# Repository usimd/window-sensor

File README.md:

# BLE window sensor for Homeassistant

BLE window/door sensor built around the u-blox NORA-B226 (nRF54L10). Broadcasts open/closed/tilt state via BTHome v2 non-connectable advertising. MCUboot OTA-capable.

## Hardware

- **MCU**: nRF54L10 (Cortex-M33, 1 MiB RRAM, 192 KB RAM) in u-blox NORA-B226-00B module
- **Sensor**: TMAG5273 3D Hall-effect sensor for contactless magnet detection
- **Power**: CR14250 (½AA) lithium cell, target multi-year battery life
- **Enclosure**: 3D-printed case with magnet holder (FreeCAD, `case/`)

## Firmware

Rust + Embassy async runtime, BLE via nrf-sdc + trouble-host.

- Non-connectable BTHome v2 advertising (open / closed / tilt)
- MCUboot bootloader with ed25519-signed OTA images
- Host-side unit tests for classifier and gesture logic

## Repository Structure

| Path | Description |
|---|---|
| `*.kicad_*` | KiCad 10 schematic, PCB, and project files |
| `lib/` | Local symbol/footprint libraries and 3D models |
| `firmware/` | Rust firmware (Embassy, BLE, MCUboot support) |
| `firmware/mcuboot/` | MCUboot config and partition overlay |
| `case/` | FreeCAD enclosure design and 3MF exports |
| `scripts/` | BLE scanner and dev utilities |
| `sim/` | Magnetic simulation data |

## Building

```bash
# Install toolchain
rustup target add thumbv8m.main-none-eabihf
cargo install just cargo-binutils

# Build, lint, test
just ci

# Flash (requires probe-rs + debug probe)
just run
```

## License

Dual-licensed: hardware under CERN-OHL-W-2.0, firmware under Apache-2.0. See [`LICENSE`](LICENSE).

## AISLER discount

In case you want to build this (or any other) project at AISLER, here's a 10€ discount code for you: `MakeInEurope-ZDCTN`.

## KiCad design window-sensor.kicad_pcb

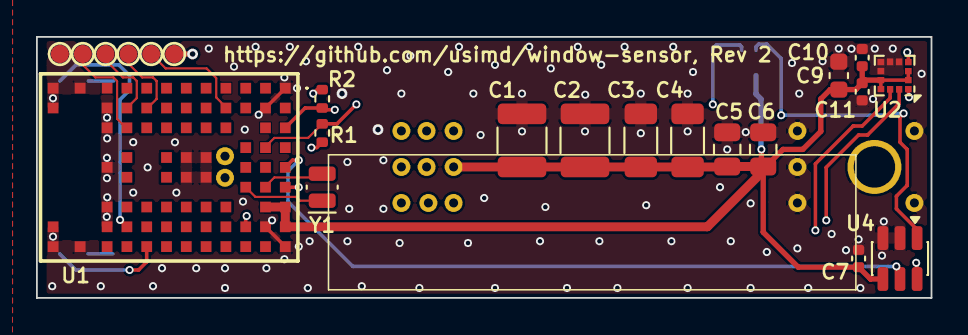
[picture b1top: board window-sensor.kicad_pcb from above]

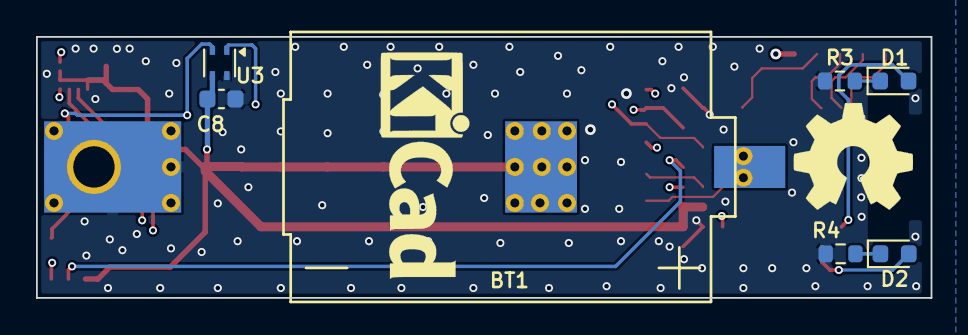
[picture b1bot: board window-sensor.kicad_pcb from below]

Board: 4 copper layers, 49.7 x 14.5 mm, 24 parts (7 on the bottom side), 17 nets.

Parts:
BT1: 1/2 AA LiSOCl2 3.6V 1200mAh; Battery_0.5AA_Keystone_557_5331
C1, C2: 47uF 10V X7R; C_1210_3225Metric
C3, C4: 22uF 10V X7R; C_1206_3216Metric
C5, C6: 10uF 10V X7R; C_0805_2012Metric
C7, C10, C11: 1uF; C_0402_1005Metric
C8: 1uF; C_0603_1608Metric
C9: 10uF; C_0603_1608Metric
D1: Blue; LED_0603_1608Metric
D2: Red; LED_0603_1608Metric
J1: Conn_01x06; Conn_01x06_PogoPins_1.27mm
R1, R2: 16.9k; R_0402_1005Metric
R3: 60.4; R_0603_1608Metric
R4: 160; R_0603_1608Metric
U1: NORA-B216-00B; NORAB22600B
U2: LIS2DTW12TR; LGA-12_2x2mm_P0.5mm
U3: SHT4x; Sensirion_DFN-4_1.5x1.5mm_P0.8mm_SHT4x_NoCentralPad
U4: TMAG5273; SOT-23-6
Y1: 32.768kHz; Crystal_SMD_MicroCrystal_CC8V-T1A-2Pin_2.0x1.2mm

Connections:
+BATT: BT1.1 (+), C1.1, C2.1, C3.1, C4.1, C5.1, C6.1, C7.1, C8.1, C9.1, C10.1, C11.1, J1.1, R1.1, R2.1, U1.A7 (VCC), U1.A8 (VCC_2), U1.B7 (VCC_3), U2.2 (~CS), U2.3 (SA0/SDO), U2.9 (Vdd), U2.10 (Vdd_IO), U3.3 (VDD), U4.4 (VCC)
/HALL: U1.A5 (GPIO_1), U4.5 (~INT)
/MEMS_INT1: U1.A6 (GPIO_2), U2.12 (INT1)
/MEMS_INT2: U1.C8 (GPIO_3), U2.11 (INT2)
/SCL: R2.2, U1.A3 (I2C_SCL), U2.1 (SCL/SPC), U3.2 (SCL), U4.1 (SCL)
/SDA: R1.2, U1.B4 (I2C_SDA), U2.4 (SDA/SDI), U3.1 (SDA), U4.6 (SDA)
/SWCLK: J1.4, U1.J2 (SWDCLK)
/SWDIO: J1.3, U1.H2 (SWDIO)
/UART_TX: J1.2, U1.D2 (QSPI_D0)
/~RESET: J1.5, U1.J3 (RESET_N)
GND: BT1.2 (-), C1.2, C2.2, C3.2, C4.2, C5.2, C6.2, C7.2, C8.2, C9.2, C10.2, C11.2, J1.6, R3.2, R4.2, U1.A1 (GND), U1.A9 (VSS_2), U1.B2 (VSS_3), U1.B8 (VSS_4), U1.E4 (VSS_5), U1.E5 (VSS_6), U1.F4 (VSS_7), U1.F5 (VSS_8), U1.K2 (VSS_9), U1.K3 (VSS_10), U1.K5 (VSS_11), U1.K7 (VSS_12), U1.K8 (VSS_13), U1.L1 (EAGP_1), U1.L9 (EAGP_2), U1.M1 (EAGP_3), U1.M2 (EAGP_4), U1.M8 (EAGP_5), U1.M9 (EAGP_6), U2.5 (RES), U2.6 (GND), U2.7 (GND), U2.8 (GND), U3.4 (VSS), U4.2 (GND), U4.3 (TEST)
unnamed: D1.2 (A), U1.J8 (GPIO_8)
unnamed: D1.1 (K), R3.1
unnamed: D2.2 (A), U1.H9 (GPIO_7)
unnamed: D2.1 (K), R4.1
unnamed: U1.B6 (XTAL_32K_1), Y1.2
unnamed: U1.C6 (XTAL_32K_2), Y1.1

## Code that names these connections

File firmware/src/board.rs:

//! Pin assignments for NORA-B216 module (nRF54L10)
//!
//! Derived from PCB netlist (window-sensor.kicad_pcb) — this is the source of truth.
//!
//! NORA-B216 module pin → nRF54L10 GPIO mapping (from UBX-24071142 product spec):
//!   A3 (I2C_SCL)  → P1.02
//!   B4 (I2C_SDA)  → P1.03
//!   A5 (GPIO_1)   → P1.04  → /HALL (TMAG5273 INT)
//!   A6 (GPIO_2)   → P1.05  → /MEMS_INT1 (LIS2DTW12 INT1)
//!   C8 (GPIO_3)   → P1.06  → /MEMS_INT2 (LIS2DTW12 INT2)
//!   H9 (GPIO_7)   → P1.10  → LED D2 (Red) anode
//!   J8 (GPIO_8)   → P1.08  → LED D1 (Blue) anode
//!   D2 (UART_TX)  → P1.01  → UART TX (debug telemetry)
//!
//! LEDs are active-high: GPIO drives anode, cathode through resistor to GND.

use embassy_nrf::peripherals;

// I2C bus (shared: TMAG5273 @ 0x22, LIS2DTW12 @ 0x19, SHT4x @ 0x44)
pub type I2cScl = peripherals::P1_02;
pub type I2cSda = peripherals::P1_03;

// Hall sensor interrupt (active-low, wake-from-sleep trigger)
pub type HallInt = peripherals::P1_04;

// MEMS accelerometer interrupts
pub type MemsInt1 = peripherals::P1_05;
pub type MemsInt2 = peripherals::P1_06;

// LEDs (active-high drive)
pub type LedBlue = peripherals::P1_08;
pub type LedRed = peripherals::P1_10;

// Debug UART TX
pub type UartTx = peripherals::P1_01;

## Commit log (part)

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2026-06-01 Initial commit: PCB, firmware, CI pipelines
    - KiCad 9 schematic + PCB (nRF54L10 / NORA-B226-00B)
    - Custom footprints + STEP models with attribution
    - Embassy/Rust firmware (BTHome v2, MCUboot OTA)
    - CI: build/test/lint + release workflow with image signing
    - Dual license: CERN-OHL-W-2.0 (hardware) + Apache-2.0 (firmware)
2026-06-01 fix(ci): use kicad/kicad:10.0 container + fix cargo fmt
    - Schematic is KiCad 10 format, sparkengineering/kicad-action@v4 ships KiCad 9
    - Replace action with direct kicad-cli commands in kicad/kicad:10.0 container
    - Fix formatting in mems.rs (long assert_eq line)
2026-06-01 fix(ci): docker run for kicad, --no-sysbuild for mcuboot
    - KiCad: container: directive breaks actions/checkout permissions;
    use docker run with volume mount instead
    - MCUboot: nRF Connect SDK v2.9.0 defaults to sysbuild which wraps
    MCUboot in multi-image build; --no-sysbuild builds bootloader standalone
2026-06-01 refactor(ci): use just recipes, bump NCS to v3.3.0, fix permissions
    - CI firmware job now calls 'just ci' + 'just sign' — same as local dev
    - KiCad docker: add --user to fix permission denied on report files
    - MCUboot: bump nRF Connect SDK to v3.3.0 (nRF54L10 board support)
    - Fix objcopy: use rust-objcopy directly (cargo objcopy arg parsing)
    - justfile: ci recipe now includes soc-heater variants, size uses cargo-binutils
2026-06-01 fix(ci): board is nrf54l15dk/nrf54l10/cpuapp in NCS v3.3.0
    The nRF54L10 doesn't have its own DK board definition in Zephyr 4.3;
    it's targeted as a SoC variant on the nRF54L15 DK.
2026-06-01 fix(ci): just var syntax, KiCad HOME=/tmp for symbol resolution
    - just variable overrides go BEFORE recipe name, not after
    - KiCad container needs HOME=/tmp so it can write .config/kicad/
    and resolve project sym-lib-table (fixes 66 phantom ERC violations)
2026-06-01 fix(ci): absolute paths for objcopy, root user for KiCad, Zephyr SDK
    - justfile objcopy: use justfile_directory() for absolute paths (fixes
    'No such file' on CI where cwd may differ)
    - KiCad docker: use --user 0:0 (root can write reports AND access
    /usr/share/kicad/template/sym-lib-table for standard symbols)
    - Release: install Zephyr SDK v0.17.0 (arm-zephyr-eabi toolchain)
    - Release: fix cargo objcopy → rust-objcopy (same arg-parsing fix)
2026-06-01 fix(ci): track .cargo/config.toml, fix KiCad sym-lib resolution
    - Add firmware/.cargo/config.toml to git (was untracked, causing cargo
    to build for x86_64 host instead of thumbv8m.main-none-eabihf on CI)
    - Copy global sym-lib-table into root's config in Docker containers so
    kicad-cli resolves standard symbol libraries when running as --user 0:0
    - Fix partitions.overlay: use &cpuapp_rram (nRF54L RRAM) instead of
    undefined &flash0 node label
2026-06-01 fix(ci): drop --user 0:0 for KiCad, fix imgtool version format
    - Run kicad-cli as default 'kicad' user (correct lib resolution),
    pre-chmod workspace for write access
    - Remove prerelease segment from imgtool versions: imgtool only
    accepts maj.min.rev[+build], not semver prerelease like -ci or -dev
2026-06-01 fix(ci): numeric imgtool version, delete-node in overlay
    - imgtool --version requires numeric build number, not hex git hash;
    use git rev-list --count HEAD instead of git rev-parse --short HEAD
    - Delete board's default partitions node before redefining to avoid
    duplicate DTS label errors (slot1_partition at two addresses)
2026-06-01 fix(ci): add pyelftools for MCUboot, ERC continue-on-error
    - MCUboot build needs pyelftools (elftools module) for post-processing
    - ERC step: continue-on-error while 3 real schematic violations exist
2026-06-01 fix(mcuboot): disable FPROTECT for nRF54L RRAM
    nRF54L uses ACL-based RRAM protection with different granularity than
    traditional flash BPROT. The 64KB bootloader region triggers a static
    assertion in FPROTECT. Disable until proper nRF54L secure boot (CRACEN)
    is configured.
2026-06-01 fix(mcuboot): shrink storage to 96KB to fit within cpuapp_rram
    nRF54L10 cpuapp_rram node is slightly under 1 MiB — Nordic's default
    layout ends at 0xFD000. Our storage at 0xE0000+128KB hit 0x100000,
    exceeding the RRAM boundary. 96KB is still plenty for NVS/settings.
2026-06-01 chore: add Renovate config, track nRF Connect SDK version
    Same base config as sibling repos (monthly, automerge non-major, dashboard
    approval for major). Custom regex manager tracks NCS_VERSION against
    nrfconnect/sdk-nrf GitHub releases.
2026-06-01 Finalize PCB before fab
2026-06-01 docs: proper README with badges, add codecov coverage
    - Board render header, AISLER fab link, CI and codecov badges
    - cargo-llvm-cov for LCOV coverage, uploaded via codecov-action
2026-06-01 docs: split license badge into HW (CERN-OHL-W) and FW (Apache-2.0)
2026-06-01 chore: docs
2026-06-01 fix: use correct codecov secret
2026-06-01 ci: integrate coverage into test flow, add integration tests
    - Replace separate 'Test with coverage' step with 'just test-cov'
    - Drop --lib from test recipes to include integration tests
    - Add firmware/tests/bthome_decode.rs integration test
2026-06-01 style: cargo fmt
2026-06-01 ci: merge coverage into ci recipe, single test pass
    test-cov replaces test in the ci recipe so coverage is always produced
    (locally and in CI). Removes separate Coverage step from workflow.
2026-06-01 fix(deps): update all non-major dependencies
2026-06-01 chore(deps): update actions/cache action to v5
2026-06-01 chore(deps): update codecov/codecov-action action to v6
2026-06-01 chore(deps): update github artifact actions
2026-06-01 chore(deps): update softprops/action-gh-release action to v3
2026-06-01 chore(deps): update github artifact actions (#4)
2026-06-01 chore(deps): update softprops/action-gh-release action to v3 (#5)
2026-06-02 Update docs, renovate and Rust build
2026-06-03 refactor(firmware): make main.rs embedded entrypoint
    - move embedded runtime entry into firmware/src/main.rs
    - remove main_embedded.rs indirection
    - gate binary with embedded-bin feature for host test isolation
    - update just recipes to pass embedded-bin only for embedded flows
    - ignore reference firmware/memory.x and rely on generated linker script
    - remove stale build.rs rerun trigger on memory.x
2026-06-03 Clean CI
2026-06-03 fix(ci): restore rustfmt compliance and relax KiCad DRC gate
    - apply cargo fmt output for firmware sources
    - mark KiCad DRC step continue-on-error like ERC to avoid blocking CI on known board violations
2026-06-03 fix(ci): resolve just target path interpolation
    Use string concatenation for artifact path variables so target expands
    correctly in CI sign/objcopy steps.
2026-06-03 fix(release): avoid stale cached MCUboot toolchain paths
    - include Zephyr SDK version in NCS workspace cache key
    - force pristine MCUboot build in CI via build-mcuboot.sh
    - make pristine mode configurable in script
2026-06-03 fix(release): build firmware binary with embedded-bin feature
    Release build-images job must enable embedded-bin so the window-sensor
    ELF exists for objcopy/signing; also pass feature to cargo size.
2026-06-03 refactor(release): use just targets in build-images job
    DRY release image build/sign/factory/size steps by calling just recipes
    used in local workflows.
2026-06-03 fix(release): keep signing key until factory image is built
2026-06-03 fix(just): make factory python command parser-safe
2026-06-07 chore(deps): update all non-major dependencies to v1.31.0
2026-06-07 chore(deps): update codecov/codecov-action action to v7
2026-06-07 chore(config): migrate config renovate.json
2026-06-07 chore(config): migrate config renovate.json (#9)
2026-06-07 chore(deps): update codecov/codecov-action action to v7 (#8)
2026-06-07 chore(deps): update all non-major dependencies to v1.31.0 (#7)

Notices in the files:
README.md:
License HW: CERN-OHL-W-2.0
